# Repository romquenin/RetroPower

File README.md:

# RetroPower

Home Assistant-controlled power module for retro consoles, built around an ESP32-C3 — 2-layer PCB (KiCad), with a relay that emulates the console's power button for remote on/off.

Consoles with a **real power switch** (SNES, NES, Mega Drive, Master System, N64, GameCube, Saturn, Dreamcast, PS1) use this board. Consoles with a **soft / momentary / touch button** (PS2, PS3, PS4 Pro, Xbox OG, Xbox 360, Wii, Wii U) need no PCB at all — just an ESP, one PhotoMOS and one resistor. That variant is documented in [`docs/soft-power-buttons.md`](docs/soft-power-buttons.md).

## Two PCB versions

### `hardware/integrated/` — integrated version (recommended)
The ESP32-C3-Zero module (Waveshare, 18 castellated pins, **antenna version isolated at the end of the board**, see the BOM warning) is **soldered directly to the back of the PCB** — no flying wires. The antenna ends up on the outer edge of the board, completely clear of any copper/metal on both sides, for the best possible WiFi/Bluetooth reception.

- Dimensions: 53.335 x 32.75 mm
- Official KiCad DRC: 0 errors / 0 warnings (v4)
- See `README.md` in this folder for the changelog and the pin-spacing verification procedure to run before soldering the module for good.

### `hardware/compact/` — compact version (fallback)
The ESP32-C3-Zero module is connected via flying wires (not soldered directly onto the PCB). Immune to dimensional variation between modules — useful as a fallback if the integrated version ever runs into a physical compatibility issue.

- Dimensions: 40.45 x 32.75 mm
- Official KiCad DRC: 0 errors / 0 warnings (v11)
- See `README.md` and `WIRING.md` in this folder.

Each folder contains: the `.kicad_pcb`/`.kicad_pro` files, the gerbers (folder + zip), the component position file (`_pos.csv`), the BOM (`BOM.csv`), a rendered image of the routed board, and a `README.md` explaining the design choices.

## Bill of materials

Full per-reference BOM (with placement notes) is in each version's own `BOM.csv` (`hardware/integrated/BOM.csv` / `hardware/compact/BOM.csv`). Same components and values on both versions, except J1 (compact version only, header for the flying wires to the ESP32) and the ESP32 module itself (soldered directly on the integrated version, wired via J1 on the compact one).

**On the PCB:**

| Ref | Part | Package | Notes |
|---|---|---|---|
| U1 | ESP32-C3-Zero (Waveshare) ⚠️ | 18-pin castellated module, 2.54mm pitch | **Version with the antenna at the end of the board, isolated from the other components** (see warning below). Integrated version only: soldered to the back of the PCB |
| K1 | HFD2/003-M-L2-D (Hongfa) | DIP-16 (10 real pins) | Bistable 2xRT relay |
| Q1, Q2 | AO3400A | SOT-23 | N-channel MOSFET |
| D1, D2 | 1N4148WS | SOD-123 | Flyback diodes (relay coils). **Orientation: the stripe (cathode) goes on the OPEN side of the rectangle on the silkscreen** |
| D3 | 1N5819WS | SOD-123 | Reverse-polarity protection on RAW_IN. **Orientation: the stripe (cathode) goes on the CLOSED side of the rectangle on the silkscreen** |
| R1, R2 | 100R | 0805, 1/4W 5% | Series gate resistors |
| R3, R4 | 10k | 0805, 1/4W 5% | Gate pulldowns |
| C1 | 100µF / 16V | SMD electrolytic, 6.3x5.4mm | — |
| C2 | 100nF | 0805 ceramic | HF decoupling on 3V3 |
| J1–J6 | 2.54mm pin headers | 2 to 5 pins, vertical | See each version's wiring notes |

> ⚠️ **Pick the right ESP32-C3 module.** Use the **Waveshare ESP32-C3-Zero** whose ceramic antenna sits **at the end of the board, set apart from the other components**. The PCB is designed so this antenna ends up on the outer edge, clear of any copper. Look-alike boards (clones, "ESP32-C3 Super Mini"…) where the antenna sits among the components, or a different pinout, will give poor Wi-Fi reception and may not fit the footprint. Check the product photos before ordering.

### ESP32-C3-Zero pin order (check before ordering)

The footprint matches the **pin order of the Waveshare ESP32-C3-Zero**. Some look-alike modules use the same size but a **different pin order**: with those, the power and GPIO pins end up in the wrong place. Compare your module with the order below before soldering.

Module seen **from its back side** (the side soldered to the PCB), antenna on the left, USB-C on the right:

| Row | Pins (antenna side → USB-C side) |
|---|---|
| Top (pins 10 → 18) | GP6 · GP7 · GP8 · GP9 · **GP10** · GP18 · GP19 · GP20 · GP21 |
| Bottom (pins 9 → 1) | GP5 · GP4 · **GP3** · GP2 · GP1 · **GP0** · **3V3** · **GND** · 5V |

Pins used by RetroPower:

| Module pin | Signal | Role |
|---|---|---|
| 2 · GND | GND | Common ground |
| 3 · 3V3 | 3V3 | Power from the 3.3 V buck (5V pin stays unconnected) |
| 4 · GP0 | POWER_SENSE | Reads the console state |
| 7 · GP3 | RELAY_SET | Relay SET (turn on) |
| 14 · GP10 | RELAY_RESET | Relay RESET (turn off), also drives the module's RGB LED |

<!-- Photo of the correct module (back side, pin labels visible): add it as docs/images/esp32-c3-zero-pinout.jpg and uncomment the line below.

-->

Full details and the pin-spacing check: [`hardware/integrated/README.md`](hardware/integrated/README.md).

**Off the PCB (external, per console):**

- A buck converter module (raw 12V/8V → regulated 3.3V) — any small off-the-shelf buck board rated for the console's raw voltage works; test it unloaded before wiring it in.
- Hookup wire:
  - **Power lines** (raw 12V/8V to/from the buck, regulated 3V3 to J2): 0.5mm²/20-21AWG is plenty for these currents.
  - **Signal/GPIO lines** (console switch tap to J4/J5, POWER_SENSE tap to J6): thinner wire is fine here, e.g. 30AWG — negligible current, easier to route inside the console's case.

## Firmware

ESPHome configs, in `firmware/`. Duplicate the template that matches your build and change `device_name` / `friendly_name` / the static IP — **one unique IP per console**.

| File | For |
|---|---|
| `retropower_template.yaml` | Relay board + ESP32-C3-Zero (validated on a SNES) |
| `retropower_template_esp8266.yaml` | Relay board + D1 mini (validated on a Master System) |
| `retropower_ps2.yaml` | PS2 fat — relay, momentary button |
| `retropower_ps4.yaml` | PS4 Pro — PhotoMOS, no relay |
| `retropower_xbox_og.yaml` | Xbox OG — PhotoMOS, no relay |
| `retropower_wii.yaml` | Wii — bare ESP-12F + PhotoMOS, no relay |
| `retropower_wiiu.yaml` | Wii U — bare ESP-12F + PhotoMOS, no relay |

Pinout on the **ESP32-C3** board:

- GPIO0 — `POWER_SENSE` (reads the console's 3V3 rail)
- GPIO3 — `RELAY_SET` (100 ms pulse → turns on, via Q1)
- GPIO10 — `RELAY_RESET` (100 ms pulse → turns off, via Q2)

Same board with a **D1 mini** soldered in instead (ESP8266: GPIO0 is a boot strapping pin, GPIO3 is the serial RX and GPIO10 is not brought out, so the three pins have to move):

- GPIO14 / `D5` — `POWER_SENSE`
- GPIO5 / `D1` — `RELAY_SET`
- GPIO4 / `D2` — `RELAY_RESET`

The `D0`–`D8` labels are silkscreen only and have nothing to do with the GPIO numbers — always write the GPIO number in the YAML.

On the **no-relay** builds, a single `output` drives the PhotoMOS (`GPIO4` / `D2`, through a 470 Ω) and `GPIO14` / `D5` reads the sense. The press duration is what distinguishes power-on, standby and forced shutdown, and it has to be measured per console.

## Per-console notes

Measurements, wiring and lessons learned for each console tested so far are in [`docs/consoles/`](docs/consoles/README.md).

## Related projects

- [`projects/toslink-switch-wifi/`](projects/toslink-switch-wifi/README.md) — Wi-Fi control of a CSL 41811 Toslink audio switch (ESPHome on a D1 mini, MOSFET on the IR-jack signal line), so the audio input follows the console that is running.

## Generation scripts (KiCad / Python)

`scripts/` contains the Python scripts (using the `pcbnew` API) used to generate and route each board, plus the verification scripts (clearance, holes, connectivity, board-edge clearance, silkscreen, component-body overlap) used alongside KiCad's official DRC.

- `scripts/integrated/`: `build_integrated.py` (placement + footprints), `route_integrated.py` (initial routing), `fix_net_integrated.py` (targeted routing fixes)
- `scripts/compact/`: `build_compact_v3.py`, `route_grid_compact5.py`
- `scripts/checks/`: verification scripts shared by both versions

Requires KiCad 7 (headless `pcbnew` API) and Python 3.

## How it works

The module emulates pressing the console's power button through two separate pulses (SET/RESET) driven by two MOSFETs (Q1/Q2) that control the two coils of a bistable relay (K1) — the relay stays in the chosen state with no continuous power draw. A sense tap (`POWER_SENSE`) lets the ESP32 read the console's actual power state for Home Assistant.

## Power supply

The buck converter (console's raw 12V/8V → regulated 3.3V) is **external**, not integrated onto the PCB. See each version's `README.md`/`WIRING.md` for the exact wiring (`J2` = regulated 3.3V input, `J3` = raw tap + reverse-polarity protection).

## Disclaimer

These files are provided as-is, with no warranty. Always re-run KiCad's official DRC before ordering a batch of PCBs, and check the 3V3 rail with a multimeter before soldering an ESP32 module in for good.

## Assembly notes (validated on a SNES, integrated board)

- **D1/D2 (flyback, 1N4148WS):** in KiCad's `D_SOD-123` footprint pad 1 is the *cathode*. The cathode must go to 3V3, so mount D1/D2 **rotated 180° vs the silkscreen** (stripe toward the 3V3 pad). **D3** is mounted as per the silkscreen.
- **GP0 (U1 pin 4) must be soldered** - it carries POWER_SENSE. Without it Home Assistant never sees the console state.
- Connect the J6 sense wire to the console's 3.3V rail; grounds must be common (buck GND on the console motherboard).
- J4: use COM (square) + NO, in parallel with the original power switch.

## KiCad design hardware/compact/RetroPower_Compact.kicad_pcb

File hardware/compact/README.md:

RetroPower - Central module, COMPACT version -- fix for 3 copper_edge_clearance errors
========================================================================
Dimensions: 40.45 x 32.75mm (UNCHANGED). Component layout UNCHANGED.
Schematic/wiring UNCHANGED (D3 remains correct, see previous version).

WHY THIS NEW VERSION
------------------------------------
Your last official DRC run found 3 [copper_edge_clearance] errors -- all
on the Q1_GATE net (the trace connecting R1, Q1 and R3), at three
different spots: (10.4, 0.2), (24.4, 0.2) and (4.8, 5.8). In all three
cases, KiCad measured only 0.025mm between this trace and the board
outline (Edge.Cuts), while the board's rules require 0.5mm.

WHAT THIS ACTUALLY MEANS
--------------------------------------
The "board outline" (Edge.Cuts) is the line the manufacturer's router (or
laser) follows to cut your board out of the raw copper/fiberglass panel.
This cut is never perfectly precise -- there's always a small mechanical
tolerance. If a copper trace runs too close to this cut line (here, 25
microns -- about the width of a fine hair), there's a real risk the
cutter "eats into" part of the trace, or even severs it completely,
without this necessarily being visible to the naked eye. Hence the 0.5mm
safety margin rule.

WHERE THIS CAME FROM
-------------------
My targeted fix tool (the one I use to repair a single copper trace
without touching the rest of the board) did have a safety margin near
the board outline, but it was only 0.3mm -- below the 0.5mm actually
required. Since the Q1_GATE net is precisely the one I had to repair
several times during the D3 fix (the board is very dense in that area,
squeezed between relay K1 and several other traces), it's the only one
that ended up going through that tool with an insufficient margin --
which explains why it alone was affected.

Digging further (checking that the fixed trace really respects 0.5mm
everywhere, not just at the 3 spots your DRC flagged), I found a second,
more subtle issue in that same tool: the safety margin near the edge
didn't account for a via's own size (a connection pad between the two
copper layers, 0.4mm radius) -- it only protected its center, not its
actual outline. A via could therefore have been allowed at a spot where
its own body still ran too close to the edge. Also fixed: the margin is
now computed separately for a trace (0.5mm + half the trace width) and
for a via (0.5mm + its actual radius).

WHAT WAS FIXED
------------------------
1. The safety margin near the board outline, in the targeted fix tool,
   was changed from 0.3mm to a value that always guarantees at least
   0.5mm of real copper clearance at the edge -- separately for traces
   and for vias (see above).
2. The Q1_GATE net was entirely ripped up and rerouted with this
   corrected margin. Since the area is very congested (the direct path
   between Q1 and R1/R3 is blocked on both sides by the already-placed
   3V3, GND and RESET_CTRL traces), it had to be routed with a finer
   calculation grid to find a path that respects both the 0.5mm board-
   edge margin AND the 0.2mm minimum trace/pad clearance -- both were
   possible to satisfy together, just not with the coarse calculation
   grid used until then.
3. A new verification tool was built specifically for this rule (none of
   my previous tools checked the board outline at all -- a complete
   blind spot, now covered). It first reproduced EXACTLY the 3 values
   from your official DRC (0.025mm at the same three coordinates) before
   I fixed anything, to make sure it was measuring the same thing as
   KiCad before relying on it to validate the fix.

WHAT WAS RE-VERIFIED (the whole board, not just Q1_GATE)
--------------------------------------------------------------------
- Distance to the board outline (new rule checked): 0 violations across
  the whole board (0 traces, 0 vias, 0 pads closer than 0.5mm from the
  edge).
- Electrical clearance (exact pad geometry, vias included): 0 violations
  across 558 elements.
- Real connectivity (correct copper layer everywhere): 0 open circuits,
  0 dangling ends.
- Hole-to-hole spacing: 0 violations across 82 holes.
- Silkscreen overlap: 0 overlaps.
- Component body overlap: 0 real overlaps (the 7 already-known and
  accepted 0.25-0.30mm close calls from the start of the project remain,
  confirmed harmless by your own DRC across several versions).

Nothing else changed on the board: same component placement, same
electrical schematic (D3 correct), same dimensions. Only the physical
path of the Q1_GATE trace changed to respect the edge safety margin.

WHAT'S LEFT TO DO BEFORE ORDERING
---------------------------------------------
1. IMPORTANT: re-run KiCad's official DRC on this fixed file -- as
   always, that check matters most.
2. Visually review the routing on screen, area by area (the Q1_GATE path
   is a bit more winding than before because of the very limited space
   around K1 -- that's normal and expected, it remains a continuous
   trace with 0 defects).
3. Measure the ESP32 board you're actually using to confirm the "ESP32
   zone" rectangle roughly matches.
4. The buck stays external and MUST be tested unloaded before wiring it
   in.
5. Check that 40.45 x 32.75mm fits the intended enclosure before
   ordering fabrication.
6. Before plugging in the ESP32 for the first time: measure the voltage
   on the PCB's 3V3 rail with a multimeter (between a 3V3 pad and a GND
   pad) BEFORE inserting the ESP32 module -- you should read ~3.3V, not
   ~12V (verification of the D3 fix, still valid).

FILES PROVIDED
-------------------
- RetroPower_Compact.kicad_pcb: the complete, fixed PCB (open in KiCad)
- RetroPower_Compact.kicad_pro: minimal project file
- gerbers_RetroPower_Compact.zip: Gerbers + drill + position file
- RetroPower_Compact_pos.csv: position/orientation of each component
- BOM.csv: component list (unchanged from the previous version)
- final_compact.png: visual render of the fixed routing

Board dimensions: 40.45 x 32.75 mm, no mounting holes.

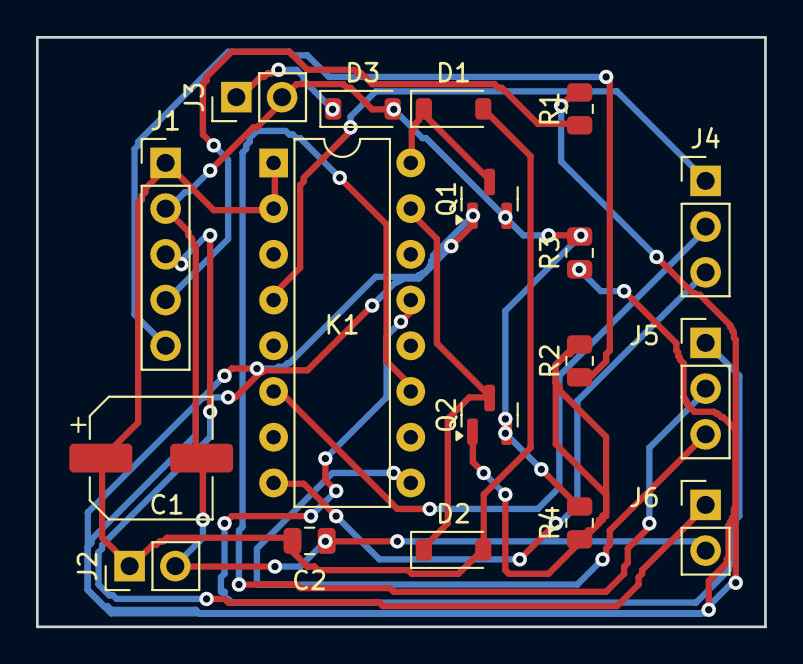
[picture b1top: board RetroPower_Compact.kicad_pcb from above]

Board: 2 copper layers, 40.5 x 32.8 mm, 18 parts (0 on the bottom side), 16 nets.

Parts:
C1: 100uF/16V (CMS); CP_Elec_6.3x5.4
C2: 100nF; C_0805_2012Metric
D1, D2: 1N4148WS (SOD-123); D_SOD-123
D3: 1N5819WS (SOD-123); D_SOD-123
J1: ESP32 (fils volants); PinHeader_1x05_P2.54mm_Vertical
J2: Buck 3V3 OUT; PinHeader_1x02_P2.54mm_Vertical
J3: Tap alim brute (vers buck); PinHeader_1x02_P2.54mm_Vertical
J4: Switch console (pole 1); PinHeader_1x03_P2.54mm_Vertical
J5: Pole 2 relais (libre/reserve); PinHeader_1x03_P2.54mm_Vertical
J6: POWER_SENSE tap console (deja 3.3V); PinHeader_1x02_P2.54mm_Vertical
K1: HFD2/003-M-L2-D; DIP-16_W7.62mm
Q1, Q2: AO3400A; SOT-23
R1, R2: 100R; R_0805_2012Metric
R3, R4: 10k; R_0805_2012Metric

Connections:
3V3: C1.1, C2.1, D1.2, D2.2, J1.1, J2.1, K1.1, K1.2
COIL_RESET_B: D2.1, K1.15, Q2.3
COIL_SET_B: D1.1, K1.16, Q1.3
GND: C1.2, C2.2, D3.2, J1.2, J2.2, J3.2, J6.2, Q1.2, Q2.2, R3.2, R4.2
Q1_GATE: Q1.1, R1.2, R3.1
Q2_GATE: Q2.1, R2.2, R4.1
RAW_IN: D3.1, J3.1
RESET_CTRL: J1.5, R2.1
SENSE_MID: J1.3, J6.1
SET_CTRL: J1.4, R1.1
SW2_COM: J5.1, K1.13
SW2_NC: J5.2, K1.11
SW2_NO: J5.3, K1.9
SW_COM: J4.1, K1.4
SW_NC: J4.2, K1.6
SW_NO: J4.3, K1.8
